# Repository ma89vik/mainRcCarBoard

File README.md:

# Main Control Board for Radio Controlled Car

# Pre-Requirements
 * CMake installed

# Building the project
 * Set TOOLCHAIN_PATH to the path to your arm-none-eabi folder if toolchain not in path
 * Install python requirements from requirements.txt

# Features
 * Bootloader with ECDSA signature verification

# TODO
 * SHA hardware acceleration
 * Define and implement control board <-> nav board protocol (protobuf)

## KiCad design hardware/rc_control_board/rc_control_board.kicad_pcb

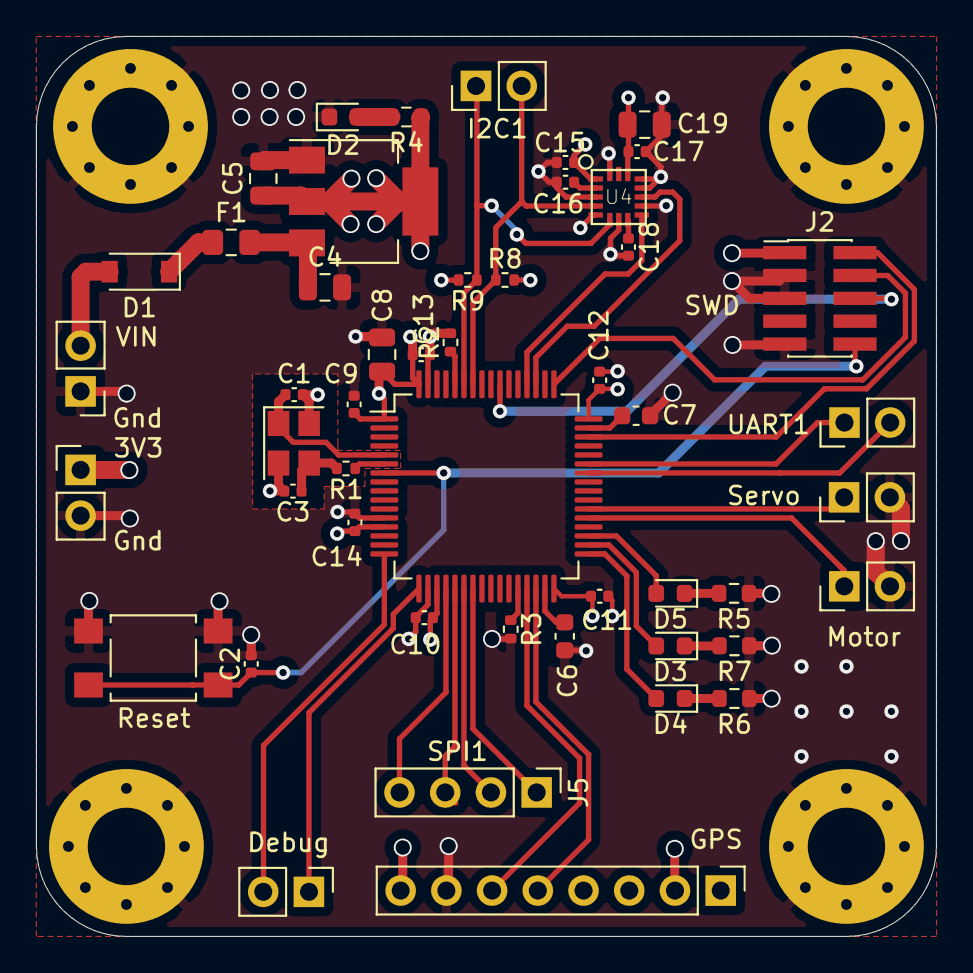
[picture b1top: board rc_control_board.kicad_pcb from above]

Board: 4 copper layers, 50.0 x 50.0 mm, 53 parts (0 on the bottom side), 41 nets.

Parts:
C1, C3: 12p; C_0402_1005Metric
C2, C9, C10, C11, C12, C13, C14, C15, C16, C17, C18: 100n; C_0402_1005Metric
C4, C5: 10u; C_0805_2012Metric
C6, C7: 2.2n; C_0603_1608Metric
C8, C19: 4.7u; C_0805_2012Metric
D1: B5819W; D_SOD-123
D2: PWR_LED; LED_0603_1608Metric
D3: LED_GREEN; LED_0603_1608Metric
D4: LED_YELLOW; LED_0603_1608Metric
D5: LED_BLUE; LED_0603_1608Metric
F1: 1A; Fuse_0805_2012Metric_Pad1.15x1.40mm_HandSolder
H1, H2, H3, H4: MountingHole_Pad; MountingHole_4.3mm_M4_Pad_Via
J1: PWR; PinHeader_1x02_P2.54mm_Vertical
J2: SWD Con; PinHeader_2x05_P1.27mm_Vertical_SMD
J3: I2C1; PinHeader_1x02_P2.54mm_Vertical
J4: GPS; PinHeader_1x08_P2.54mm_Vertical
J5: SPI1; PinHeader_1x04_P2.54mm_Vertical
J6: UART_DEBUG; PinHeader_1x02_P2.54mm_Vertical
J7: UART_NAV_BOARD; PinHeader_1x02_P2.54mm_Vertical
J8: MOTOR_CTRL; PinHeader_1x02_P2.54mm_Vertical
J9: SERVO_CTRL; PinHeader_1x02_P2.54mm_Vertical
J10: 3V3_Con; PinHeader_1x02_P2.54mm_Vertical
R1: 220; R_0402_1005Metric
R2, R3: 10k; R_0402_1005Metric
R4, R5, R6, R7: 2k2; R_0603_1608Metric
R8, R9: 2k2; R_0402_1005Metric
SW1: SW_Push_Dual; SW_SPST_TL3305A
U1: AMS1117-3.3; SOT-223-3_TabPin2
U2: STM32F405RGTx; LQFP-64_10x10mm_P0.5mm
U4: FXOS8700CQ; FSOS8700CQ_PKG
Y1: 16 Mhz; Crystal_SMD_3225-4Pin_3.2x2.5mm

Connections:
+3V3: C5.1, C8.2, C9.2, C10.2, C11.1, C12.1, C13.1, C14.1, C15.2, C17.1, C19.1, J2.1, J4.2, J4.8, J10.1, R4.1, R8.2, R9.2, U1.2, U2.1, U2.13, U2.19, U2.32, U2.48, U2.64, U4.P$1, U4.P$14
BOOT0: R2.1, U2.60
BOOT1: R3.1, U2.28
GND: C1.2, C2.2, C3.2, C4.2, C5.2, C6.2, C7.2, C8.1, C9.1, C10.1, C11.2, C12.2, C13.2, C14.2, C15.1, C16.1, C17.2, C18.2, C19.2, D2.1, H1.1, H2.1, H3.1, H4.1, J1.1, J2.3, J2.5, J2.9, J4.7, J8.2, J9.2, J10.2, R2.2, R3.2, R5.1, R6.1, R7.1, SW1.1, U1.1, U2.12, U2.18, U2.63, U4.P$3, U4.P$5, U4.P$7, U4.P$10, U4.P$12, U4.P$13, U4.P$16, Y1.2, Y1.4
HSE_IN: C1.1, U2.5, Y1.1
HSE_OUT: R1.1, U2.6
I2C1_SCL: J3.2, R8.1, U2.58, U4.P$4
I2C1_SDA: J3.1, R9.1, U2.59, U4.P$6
IMU_INT1: U2.51, U4.P$11
IMU_INT2: U2.52, U4.P$9
LED_BLUE: D5.2, U2.35
LED_GREEN: D3.2, U2.34
LED_YELLOW: D4.2, U2.33
MOTOR_PWM: J8.1, U2.37
unnamed: C3.1, R1.2, Y1.3
unnamed: C4.1, F1.2, U1.3
unnamed: C6.1, U2.31
unnamed: C7.1, U2.47
unnamed: C16.2, U4.P$2
unnamed: C18.1, U4.P$8
unnamed: D1.1, F1.1
unnamed: D1.2, J1.2
unnamed: D2.2, R4.2
unnamed: D3.1, R7.2
unnamed: D4.1, R6.2
unnamed: D5.1, R5.2
RST: C2.1, J2.10, SW1.2, U2.7
SERVO_PWM: J9.1, U2.38
SPI1_CS: J5.4, U2.20
SPI1_MISO: J5.2, U2.22
SPI1_MOSI: J5.1, U2.23
SPI1_SCK: J5.3, U2.21
SWD_CLK: J2.4, U2.49
SWD_IO: J2.2, U2.46
SWO: J2.6, U2.55
UART1_RX: J7.1, U2.43
UART1_TX: J7.2, U2.42
UART2_RX: J6.1, U2.17
UART2_TX: J6.2, U2.16
UART3_RX: J4.5, U2.30
UART3_TX: J4.6, U2.29

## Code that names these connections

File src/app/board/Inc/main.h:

/* USER CODE BEGIN Header */
/**
  ******************************************************************************
  * @file           : main.h
  * @brief          : Header for main.c file.
  *                   This file contains the common defines of the application.
  ******************************************************************************
  * @attention
  *
  * <h2><center>&copy; Copyright (c) 2020 STMicroelectronics.
  * All rights reserved.</center></h2>
  *
  * This software component is licensed by ST under Ultimate Liberty license
  * SLA0044, the "License"; You may not use this file except in compliance with
  * the License. You may obtain a copy of the License at:
  *                             www.st.com/SLA0044
  *
  ******************************************************************************
  */
/* USER CODE END Header */

/* Define to prevent recursive inclusion -------------------------------------*/
#ifndef __MAIN_H
#define __MAIN_H

#ifdef __cplusplus
extern "C" {
#endif

/* Includes ------------------------------------------------------------------*/
#include "stm32f4xx_hal.h"
#include "stm32f4xx_hal.h"

/* Private includes ----------------------------------------------------------*/
/* USER CODE BEGIN Includes */

/* USER CODE END Includes */

/* Exported types ------------------------------------------------------------*/
/* USER CODE BEGIN ET */

/* USER CODE END ET */

/* Exported constants --------------------------------------------------------*/
/* USER CODE BEGIN EC */

/* USER CODE END EC */

/* Exported macro ------------------------------------------------------------*/
/* USER CODE BEGIN EM */

/* USER CODE END EM */

/* Exported functions prototypes ---------------------------------------------*/
void Error_Handler(void);

/* USER CODE BEGIN EFP */

/* USER CODE END EFP */

/* Private defines -----------------------------------------------------------*/
#define DEBUG_TX_Pin GPIO_PIN_2
#define DEBUG_TX_GPIO_Port GPIOA
#define DEBUG_RX_Pin GPIO_PIN_3
#define DEBUG_RX_GPIO_Port GPIOA
#define GPS_TX_Pin GPIO_PIN_10
#define GPS_TX_GPIO_Port GPIOB
#define GPS_RX_Pin GPIO_PIN_11
#define GPS_RX_GPIO_Port GPIOB
#define LED_YELLOW_Pin GPIO_PIN_12
#define LED_YELLOW_GPIO_Port GPIOB
#define LED_GREEN_Pin GPIO_PIN_13
#define LED_GREEN_GPIO_Port GPIOB
#define LED_BLUE_Pin GPIO_PIN_14
#define LED_BLUE_GPIO_Port GPIOB
#define MOTOR_PWM_Pin GPIO_PIN_6
#define MOTOR_PWM_GPIO_Port GPIOC
#define SERVO_PWM_Pin GPIO_PIN_7
#define SERVO_PWM_GPIO_Port GPIOC
#define NAV_TX_Pin GPIO_PIN_9
#define NAV_TX_GPIO_Port GPIOA
#define NAV_RX_Pin GPIO_PIN_10
#define NAV_RX_GPIO_Port GPIOA
#define IMU_INT1_Pin GPIO_PIN_10
#define IMU_INT1_GPIO_Port GPIOC
#define IMU_INT2_Pin GPIO_PIN_11
#define IMU_INT2_GPIO_Port GPIOC
/* USER CODE BEGIN Private defines */

/* USER CODE END Private defines */

#ifdef __cplusplus
}
#endif

#endif /* __MAIN_H */

/************************ (C) COPYRIGHT STMicroelectronics *****END OF FILE****/

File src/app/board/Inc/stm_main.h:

/* USER CODE BEGIN Header */
/**
  ******************************************************************************
  * @file           : main.h
  * @brief          : Header for main.c file.
  *                   This file contains the common defines of the application.
  ******************************************************************************
  * @attention
  *
  * <h2><center>&copy; Copyright (c) 2019 STMicroelectronics.
  * All rights reserved.</center></h2>
  *
  * This software component is licensed by ST under Ultimate Liberty license
  * SLA0044, the "License"; You may not use this file except in compliance with
  * the License. You may obtain a copy of the License at:
  *                             www.st.com/SLA0044
  *
  ******************************************************************************
  */
/* USER CODE END Header */

/* Define to prevent recursive inclusion -------------------------------------*/
#ifndef __MAIN_H
#define __MAIN_H

#ifdef __cplusplus
extern "C" {
#endif

/* Includes ------------------------------------------------------------------*/
#include "stm32f4xx_hal.h"
#include "stm32f4xx_hal.h"

/* Private includes ----------------------------------------------------------*/
/* USER CODE BEGIN Includes */

/* USER CODE END Includes */

/* Exported types ------------------------------------------------------------*/
/* USER CODE BEGIN ET */

/* USER CODE END ET */

/* Exported constants --------------------------------------------------------*/
/* USER CODE BEGIN EC */

/* USER CODE END EC */

/* Exported macro ------------------------------------------------------------*/
/* USER CODE BEGIN EM */

/* USER CODE END EM */

/* Exported functions prototypes ---------------------------------------------*/
void Error_Handler(void);

/* USER CODE BEGIN EFP */

/* USER CODE END EFP */

/* Private defines -----------------------------------------------------------*/
#define pulseLenUs 10
#define pulsePeriodUs 65000
#define CS_I2C_SPI_Pin GPIO_PIN_3
#define CS_I2C_SPI_GPIO_Port GPIOE
#define PC14_OSC32_IN_Pin GPIO_PIN_14
#define PC14_OSC32_IN_GPIO_Port GPIOC
#define PC15_OSC32_OUT_Pin GPIO_PIN_15
#define PC15_OSC32_OUT_GPIO_Port GPIOC
#define PH0_OSC_IN_Pin GPIO_PIN_0
#define PH0_OSC_IN_GPIO_Port GPIOH
#define PH1_OSC_OUT_Pin GPIO_PIN_1
#define PH1_OSC_OUT_GPIO_Port GPIOH
#define OTG_FS_PowerSwitchOn_Pin GPIO_PIN_0
#define OTG_FS_PowerSwitchOn_GPIO_Port GPIOC
#define PDM_OUT_Pin GPIO_PIN_3
#define PDM_OUT_GPIO_Port GPIOC
#define B1_Pin GPIO_PIN_0
#define B1_GPIO_Port GPIOA
#define I2S3_WS_Pin GPIO_PIN_4
#define I2S3_WS_GPIO_Port GPIOA
#define SPI1_SCK_Pin GPIO_PIN_5
#define SPI1_SCK_GPIO_Port GPIOA
#define SPI1_MISO_Pin GPIO_PIN_6
#define SPI1_MISO_GPIO_Port GPIOA
#define SPI1_MOSI_Pin GPIO_PIN_7
#define SPI1_MOSI_GPIO_Port GPIOA
#define BOOT1_Pin GPIO_PIN_2
#define BOOT1_GPIO_Port GPIOB
#define CLK_IN_Pin GPIO_PIN_10
#define CLK_IN_GPIO_Port GPIOB
#define LD4_Pin GPIO_PIN_12
#define LD4_GPIO_Port GPIOD
#define LD3_Pin GPIO_PIN_13
#define LD3_GPIO_Port GPIOD
#define LD5_Pin GPIO_PIN_14
#define LD5_GPIO_Port GPIOD
#define LD6_Pin GPIO_PIN_15
#define LD6_GPIO_Port GPIOD
#define I2S3_MCK_Pin GPIO_PIN_7
#define I2S3_MCK_GPIO_Port GPIOC
#define VBUS_FS_Pin GPIO_PIN_9
#define VBUS_FS_GPIO_Port GPIOA
#define OTG_FS_ID_Pin GPIO_PIN_10
#define OTG_FS_ID_GPIO_Port GPIOA
#define OTG_FS_DM_Pin GPIO_PIN_11
#define OTG_FS_DM_GPIO_Port GPIOA
#define OTG_FS_DP_Pin GPIO_PIN_12
#define OTG_FS_DP_GPIO_Port GPIOA
#define SWDIO_Pin GPIO_PIN_13
#define SWDIO_GPIO_Port GPIOA
#define SWCLK_Pin GPIO_PIN_14
#define SWCLK_GPIO_Port GPIOA
#define I2S3_SCK_Pin GPIO_PIN_10
#define I2S3_SCK_GPIO_Port GPIOC
#define I2S3_SD_Pin GPIO_PIN_12
#define I2S3_SD_GPIO_Port GPIOC
#define Audio_RST_Pin GPIO_PIN_4
#define Audio_RST_GPIO_Port GPIOD
#define OTG_FS_OverCurrent_Pin GPIO_PIN_5
#define OTG_FS_OverCurrent_GPIO_Port GPIOD
#define SWO_Pin GPIO_PIN_3
#define SWO_GPIO_Port GPIOB
#define Audio_SCL_Pin GPIO_PIN_6
#define Audio_SCL_GPIO_Port GPIOB
#define Audio_SDA_Pin GPIO_PIN_9
#define Audio_SDA_GPIO_Port GPIOB
#define MEMS_INT2_Pin GPIO_PIN_1
#define MEMS_INT2_GPIO_Port GPIOE
/* USER CODE BEGIN Private defines */

/* USER CODE END Private defines */

#ifdef __cplusplus
}
#endif

#endif /* __MAIN_H */

/************************ (C) COPYRIGHT STMicroelectronics *****END OF FILE****/

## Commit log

2019-03-05 Initial commit with cubemx generated code
2019-03-05 Removed unused drivers
2019-03-05 CMake config
2019-03-05 changed folder structure
2019-03-05 added missing freeRTOS files
2019-03-05 CMake fixed
2019-03-05 Compile and flash working
2019-03-06 Updated cmake with new drivers
2019-03-06 Regenerated HAL from cubemx
2019-03-07 Compiles both board and app together
2019-03-07 Copied code from nrf52
2019-03-08 Enabled UART interrupt
2019-03-08 Cleaned old nrf52 code
2019-03-10 Added PWM and car control
2019-03-14 Ported i2c to stm32 hal interface
2019-03-15 Added cmake for unit test (not working)
2019-03-15 Implemented DMA recv for uart
2019-03-17 Serial DMA + GPS implemented
2019-03-18 Add mutex for usb log
2019-03-21 Add virtual comport driver
2019-03-22 Added logger taskl
2019-03-22 Changed logger stack size
2019-03-24 Set tasks to proper frequency
2019-03-26 Update README.md
    Add TODO to readme
2019-03-28 Add protobuf
2019-04-01 Message handling for BLE serial and parsing implem
2019-04-02 Set up serial for ble board
2019-04-02 Serial testing
2019-04-03 Regenerated HAL with normal buf for DMA
2019-04-09 Added state control interface
2019-04-10 Servo/Motor control from BLE board
2019-04-12 Distance sensor added
2020-07-25 Add toolchain file for cmake
2020-07-26 build: restructure Cmake files
2020-07-26 protobuf: add cmake support, add submodule
2020-08-03 update uart driver
2020-08-09 Add led driver, add initial bootloader files
2020-08-11 Restructure bootloader layout/cmake
2020-08-19 bootloader: debug isr issue
2020-09-19 bootloader jump to app working
2020-09-19 app: add firmware image header
2020-09-24 bootloader: add printf implementation
2020-09-24 Add common component with fw header
2020-09-26 Added ECDSA app signing to image
2020-09-27 Add tinycrypt submodule
2020-09-29 Add CI build workflow
2020-09-29 CI: add gcc version
2020-09-29 CI: downgrade arm-eabi version to Q1
2020-09-29 CI: downgrade arm gcc version again
    Downgrade to a version known to be supported by the github action
2020-09-29 CI: Update cmake config command
    Add ninja + arm toolchain file
2020-09-29 CI: install ninja
2020-09-29 Build system: allow building without toolchain
    Allow building without toolchain path set if compilers are in path
2020-09-29 CI: install python dependencies
2020-09-29 CI: change container to ubuntu 20.04
2020-09-29 Build system: explicitly use python3
2020-09-29 CI: add test deploy job
2020-09-29 CI: fix yaml warning
2020-09-29 CI: use action for scp deploy
2020-09-29 Add badge to readme
2020-09-29 bootloader: add app sign check
2020-09-29 bootloader: move tinycrypt
2020-09-29 CI: checkout submodules
2020-09-29 CI: fix syntax
2020-09-29 Fix all warnings
2020-09-29 Build system: use find_package for python
2020-09-29 common: fix formating error of git SHA
2020-09-30 Bootloader: verify signature working
2020-09-30 App: fix fw hdr being optimized away on release
2020-09-30 Remove temp private signing key
2020-09-30 CI: change pip to pip3
2020-09-30 Move private key input to env variable
2020-09-30 CI: add private key secret to build
2020-09-30 CI: fix yaml syntax
2020-09-30 Bootloader: add initial commit for reset reason
2020-10-08 CI: Rename workflow
2020-10-08 Doc: update readme badge
2020-10-08 bootloader: now correctly boots app image after verificationY
2020-10-11 App: regenerated bare-bones cubemx board files
2020-10-11 app: log component added
2020-10-19 hardware: add version v1.0 of rc_control_board
2020-10-19 app: add logging + GPS uart
2020-10-24 HW: Fix layout errors for IMU
2020-10-24 app: rename log
2020-10-25 App: regenerate board files from cubemx Include freertos and more drivers
2020-10-26 app: add fault handler
2020-11-05 app: add protobuf
2020-11-05 CI: add nanopb scripts to path
2020-11-06 bootloader: bringup OK
2020-11-07 App: basic bringup OK
2020-11-07 app: bringup HSE, 168 MHz sys clock
2020-11-08 app: bringup FXOS8700
2020-11-16 app: nav_board com bringup
2020-11-16 Bump cryptography from 3.1.1 to 3.2
    Bumps [cryptography](https://github.com/pyca/cryptography) from 3.1.1 to 3.2.
    - [Release notes](https://github.com/pyca/cryptography/releases)
    - [Changelog](https://github.com/pyca/cryptography/blob/master/CHANGELOG.rst)
    - [Commits](https://github.com/pyca/cryptography/compare/3.1.1...3.2)
2020-11-16 app: car control bringup
2020-11-18 App: add nav board test gui
2020-11-21 App: motor control working
2021-02-10 Bump cryptography from 3.1.1 to 3.3.2
    Bumps [cryptography](https://github.com/pyca/cryptography) from 3.1.1 to 3.3.2.
    - [Release notes](https://github.com/pyca/cryptography/releases)
    - [Changelog](https://github.com/pyca/cryptography/blob/master/CHANGELOG.rst)
    - [Commits](https://github.com/pyca/cryptography/compare/3.1.1...3.3.2)
